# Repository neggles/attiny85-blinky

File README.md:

# attiny85-blinky
Arduino blinky shenanigans for ATtiny85/Gemma/Trinket and WS2812B LEDs.

This was written and tested using the Arduino ATtiny core from http://highlowtech.org/?p=1695, but ought to work with other cores.

Uses a hardware pin-change interrupt, and the Adafruit Neopixel library.

It has been confirmed to operate on an Adafruit GEMMA and 3.3v Trinket, though it's important to note that if your cheap WS2812B LEDs are receiving over ~4v VCC, a 3.3v micro may not be able to push the DIN pin hard enough.

Also included is an eagle .brd/.sch pair for a small CR2032-powered widget with a SOIC ATTiny85 and 4 LEDs.
Battery life isn't amazing, and you should omit/bridge the 3.3v regulator if you want it to work under USB power, so it's not perfect, but it's neat.
(I'm not actually sure why I kept the 3.3v regulator, if we're honest. It does very little at best.)

PCBs can be bought directly from OSHPark here, at about six bucks for 3: https://oshpark.com/shared_projects/sMGC09Kl

Here's a pic of a couple I made, sans USB connections since I hadn't received the sockets at this point; http://i.imgur.com/KQKQHtf.jpg

Otherwise, this code is fairly flexible and modular (on purpose) and I tried to comment it as best I could.

Let me know what you think :)

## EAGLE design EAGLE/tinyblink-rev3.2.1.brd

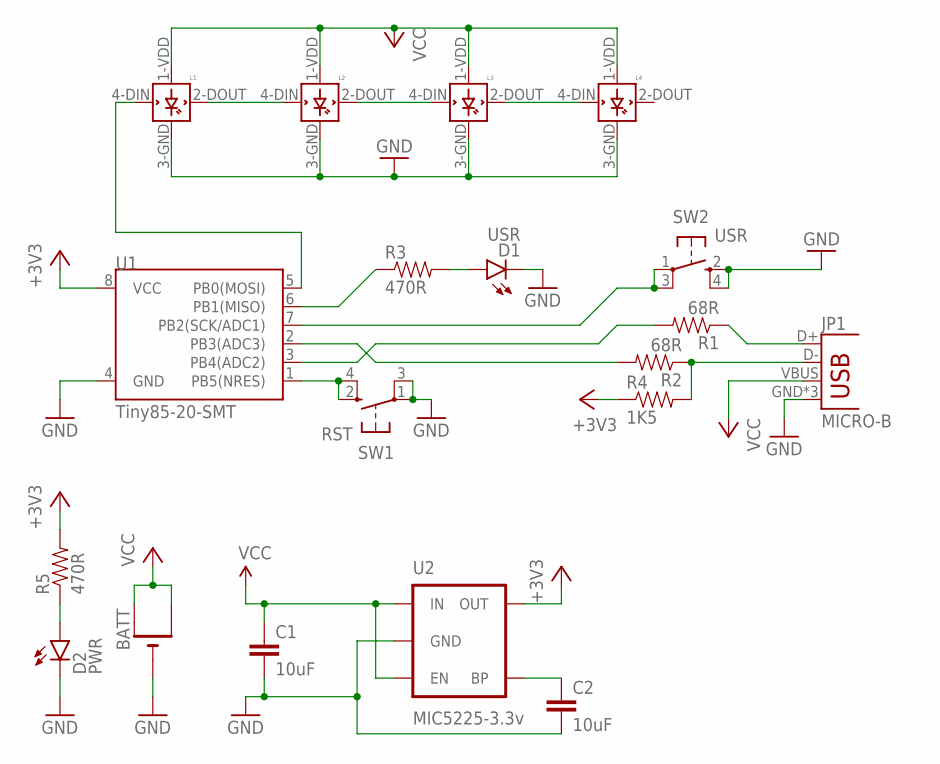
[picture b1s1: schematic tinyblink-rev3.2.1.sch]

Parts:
BATT: CR2032SMT; CR2032-SMD
C1, C2: 10uF; 0603-CAP
D1: USR; LED-0603
D2: PWR; LED-0603
JP1: MICRO-B; USB-MICROB
L1, L2, L3, L4: WS2812B
R1, R2: 68R; 0603-RES
R3, R5: 470R; 0603-RES
R4: 1K5; 0603-RES
SW1: RST; KMR2
SW2: USR; KMR2
U1: Tiny85-20-SMT; SO08-EIAJ
U2: MIC5225-3.3v; SOT23-5

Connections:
+3V3: R4.1, R5.2, U1.8 (VCC), U2.5 (OUT)
GND: BATT.-, C1.2, C2.2, D1.C, D2.C, JP1.GND, JP1.MT1 (GND), JP1.MT2 (GND), L1.3-GND (GND), L2.3-GND (GND), L3.3-GND (GND), L4.3-GND (GND), SW1.1, SW1.3 (P1), SW2.2 (S), SW2.4 (S1), U1.4 (GND), U2.2 (GND)
unnamed: SW1.2 (S), SW1.4 (S1), U1.1 (PB5(NRES))
unnamed: SW2.1, SW2.3 (P1), U1.7 (PB2(SCK/ADC1))
unnamed: L1.4-DIN (DIN), U1.5 (PB0(MOSI))
unnamed: D1.A, R3.2
unnamed: JP1.D+, R1.1
unnamed: JP1.D-, R2.1, R4.2
unnamed: C2.1, U2.4 (BP)
unnamed: L1.2-DOUT (DOUT), L2.4-DIN (DIN)
unnamed: R2.2, U1.2 (PB3(ADC3))
unnamed: D2.A, R5.1
unnamed: R1.2, U1.3 (PB4(ADC2))
unnamed: L2.2-DOUT (DOUT), L3.4-DIN (DIN)
unnamed: L3.2-DOUT (DOUT), L4.4-DIN (DIN)
unnamed: R3.1, U1.6 (PB1(MISO))
VCC: BATT.+$1 (+), BATT.+$2 (+1), C1.1, JP1.VBUS, L1.1-VDD (VDD), L2.1-VDD (VDD), L3.1-VDD (VDD), L4.1-VDD (VDD), U2.1 (IN), U2.3 (EN)

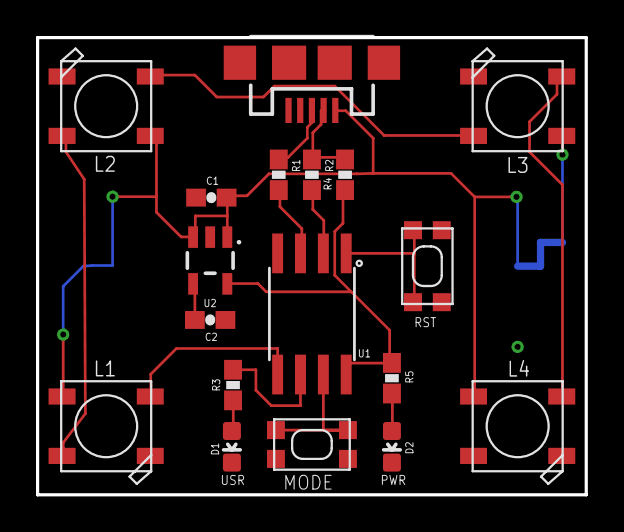
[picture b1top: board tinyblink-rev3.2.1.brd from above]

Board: 2 copper layers, 30.5 x 25.4 mm, 19 parts (1 on the bottom side), 17 nets.

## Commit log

2015-07-10 initial push

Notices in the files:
parts and their libraries:
SparkFun-Capacitors: Licensing: Creative Commons ShareAlike 4.0 International - https://creativecommons.org/licenses/by-sa/4.0
